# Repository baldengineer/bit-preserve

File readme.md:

# Bit Preserve
Recreating classic computer schematics. Let's convert all those random scanned PDFs into a modern, editiable and re-usable format.

# How it works
* Pick a system
* Find a schematic
* And start drawing!

This project uses [KiCad](http://kicad.org) for capturing schematics. 

# Notes
* If there are variants of the schematic, give them their own directory. 
* If you see a system you'd like to contribute but it isn't listed, submit a pull request. 
* If you start working on a system, please do a PR on the readme file in that directory and put your name there as "working on it." 
* Have suggestions or questions? Then [submit an issue](https://github.com/baldengineer/bit-preserve/issues)!

# More information
* Original project announcement [KiCon 2019](https://www.youtube.com/watch?v=fBaU4JZOVzk)
* See additional info on this [baldengineer.com post](https://www.baldengineer.com/bit-preserve-vintage-schematics-with-kicad.html).

# Rules - More like Guidelines
My goal is to have minimal rules. Right now I'd like to focus on documenting these systems *somewhere*. Someday, we might develop a style guide.

Bit Preserve has a few simple rules:
1. Do not upload bitmapped PDFs or images of original schematics. Instead, please link to repositories for that specific system instead.
2. Use KiCad's [Plot -> PDF] of the Schematic (not print!) when "done."
3. Add a link in the README to that PDF to make finding them easier.
4. Originally, we did not share symbol libraries between systems. (This was before KiCad changed how symbols get imported and linked in a schematic)
5. If you decide to re-create the PCB, **Please do NOT upload large binaries like STEP files**. Contact me if you want to include STEPs. (We'll do it as a submodule.)

# Questions or Ideas
Please, [submit an issue](https://github.com/baldengineer/bit-preserve/issues). In most cases, there is no need to email me. I want open discussions about how we move forward.

	-James
	@[baldengineer](https://baldengineer.com/baldengineer)

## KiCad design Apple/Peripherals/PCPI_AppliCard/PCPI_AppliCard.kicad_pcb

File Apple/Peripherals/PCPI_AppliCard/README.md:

# PCPI AppliCard

This is a clone of the PCPI AppliCard, a Z80 coprocessor card for the Apple II.
I've previously captured the [Microsoft Softcard](https://git.alfter.us/salfter/Microsoft_Softcard),
a simpler Z80 board that uses the Apple II's memory.  This board has its own
64K (expandable to 192K) connected directly to the Z80 and running at the same
speed.

The schematic was captured from published sources.  The PCB layout is based on
the component layout shown in a photo of the original board, but the connections
between components are my own work.  The new PCB, like the original, is a 2-layer
design.

I've not had a chance to build this.  DRC tells me the PCB matches the schematic.
I think my schematic capture is correct, but I don't have a working PCB to compare
against, so **use this at your own risk**.

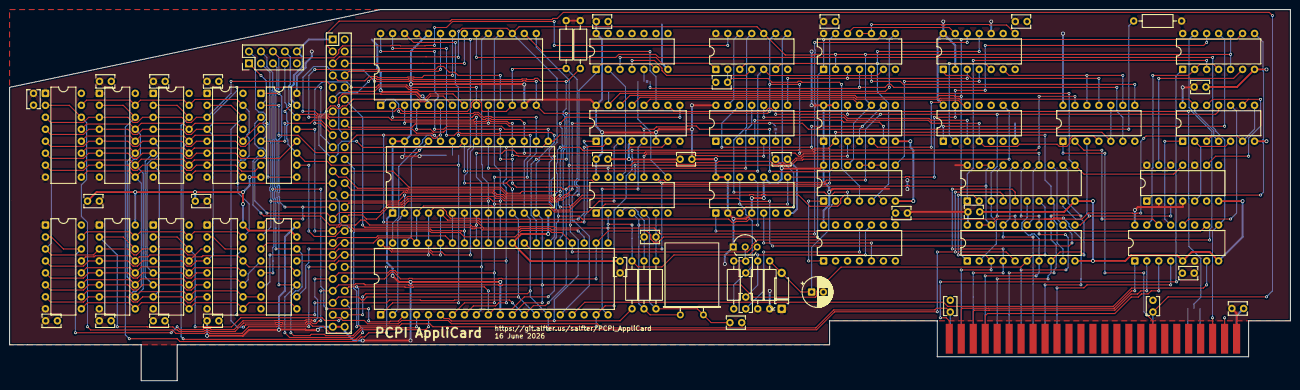
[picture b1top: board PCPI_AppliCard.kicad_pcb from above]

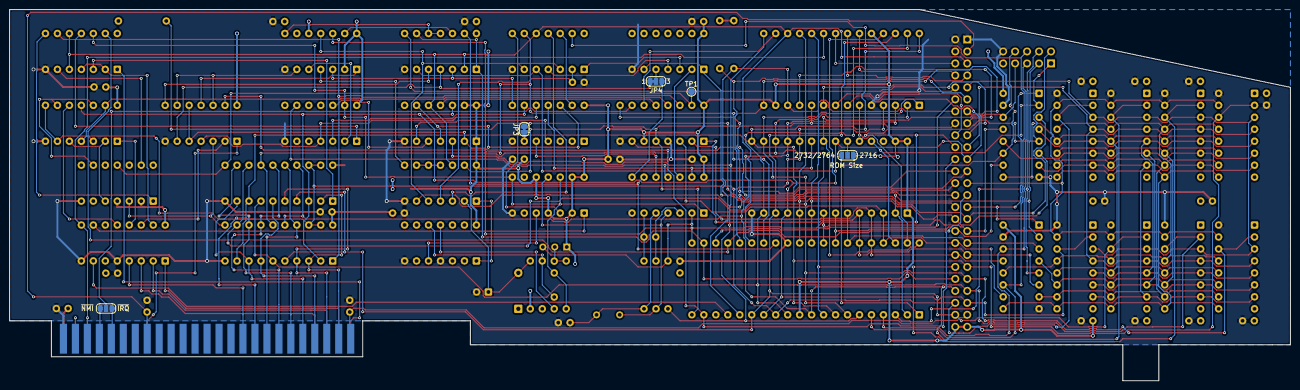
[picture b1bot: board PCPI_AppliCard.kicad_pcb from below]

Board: 2 copper layers, 271.8 x 78.7 mm, 82 parts (5 on the bottom side), 143 nets.

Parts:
C1, C2, C3, C4, C5, C6, C7, C8, C9, C10, C11, C13, C14, C15, C18, C19, C21, C22, C23, C24, C27, C28, C29, C30: 0.1 µF; C_Disc_D3.8mm_W2.6mm_P2.50mm
C12: 0.01 µF; C_Disc_D3.8mm_W2.6mm_P2.50mm
C16: 1000 pF; C_Disc_D3.8mm_W2.6mm_P2.50mm
C17, C31: 33 pF; C_Disc_D3.8mm_W2.6mm_P2.50mm
C20: 100 µF; CP_Radial_D6.3mm_P2.50mm
C25: 47 pF; C_Disc_D3.8mm_W2.6mm_P2.50mm
CR1: 1N4148; D_A-405_P7.62mm_Horizontal
JP1: IRQ/NMI; SolderJumper-3_P1.3mm_Open_RoundedPad1.0x1.5mm_NumberLabels
JP2: ROM_Size; SolderJumper-3_P1.3mm_Open_RoundedPad1.0x1.5mm_NumberLabels
JP3: SolderJumper_2_Bridged; SolderJumper-2_P1.3mm_Bridged_RoundedPad1.0x1.5mm
JP4: SolderJumper_3_Bridged12; SolderJumper-3_P1.3mm_Bridged12_RoundedPad1.0x1.5mm_NumberL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
P1: apple2-bus-edgeconn; Male_Card-Edge_50_pin__100_mil
P2: Conn_02x25_Counter_Clockwise; PinHeader_2x25_P2.54mm_Vertical_Counterclockwise
P3: Conn_02x05_Counter_Clockwise; PinHeader_2x05_P2.54mm_Vertical_Counterclockwise
Q1: 2N2907A; TO-92L_Inline_Wide
R1, R2, R3: 4.7 kΩ; R_Axial_DIN0207_L6.3mm_D2.5mm_P10.16mm_Horizontal
R4: 82 kΩ; R_Axial_DIN0207_L6.3mm_D2.5mm_P10.16mm_Horizontal
R5, R6: 1 kΩ; R_Axial_DIN0207_L6.3mm_D2.5mm_P10.16mm_Horizontal
R7: 27 Ω; R_Axial_DIN0207_L6.3mm_D2.5mm_P10.16mm_Horizontal
R8, R9: 10 kΩ; R_Axial_DIN0207_L6.3mm_D2.5mm_P10.16mm_Horizontal
TP1: TestPoint_Pad_D1.5mm
U1, U2, U3, U4, U5, U6, U7, U8: MK4164; DIP-16_W7.62mm
U9, U10: SN74LS158N; DIP-16_W7.62mm
U11: Z84C0006PEG; DIP-40_W15.24mm
U12: 2764; DIP-28_W15.24mm
U13: Z84C3006PEG; DIP-28_W15.24mm
U14, U19: SN74LS04N; DIP-14_W7.62mm
U15, U29: SN74LS138N; DIP-16_W7.62mm
U16, U28: SN74LS32N; DIP-14_W7.62mm
U17, U22, U27, U30: SN74LS74AN; DIP-14_W7.62mm
U18: SN74LS00N; DIP-14_W7.62mm
U20: SN74121N; DIP-14_W7.62mm
U21: SN74LS132N; DIP-14_W7.62mm
U23: SN74LS11N; DIP-14_W7.62mm
U24, U25: SN74LS374N; DIP-20_W7.62mm
U26: SN74LS393N; DIP-14_W7.62mm
U31: SN74LS125AN; DIP-14_W7.62mm
U32: SN74LS08N; DIP-14_W7.62mm
Y1: 12 MHz; Crystal_HC49-U_Horizontal

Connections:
+5V: C1.1, C2.1, C3.1, C4.1, C5.1, C6.1, C7.1, C8.1, C9.1, C10.1, C11.1, C13.1, C14.1, C15.1, C18.1, C19.1, C21.1, C22.1, C24.1, C27.1, C29.1, C30.1, CR1.1 (K), JP2.1 (A), P1.25 (+5V), P2.25, P2.26, Q1.1 (E), R1.1, R2.1, R3.1, R8.2, R9.1, U1.1 (~RFSH), U1.8 (VCC), U2.1 (~RFSH), U2.8 (VCC), U3.1 (~RFSH), U3.8 (VCC), U4.1 (~RFSH), U4.8 (VCC), U5.1 (~RFSH), U5.8 (VCC), U6.1 (~RFSH), U6.8 (VCC), U7.1 (~RFSH), U7.8 (VCC), U8.1 (~RFSH), U8.8 (VCC), U9.16 (VCC), U10.16 (VCC), U11.11 (V_{CC}), U12.1 (VPP), U12.27 (~PGM), U12.28 (VCC), U13.13 (IEI), U13.24 (VCC), U14.14 (VCC), U15.6 (E3), U15.16 (VCC), U16.14 (VCC), U17.2 (D), U17.4 (~S), U17.10 (~S), U17.13 (~R), U17.14 (VCC), U18.14 (VCC), U19.14 (VCC), U20.14 (VCC), U21.14 (VCC), U22.1 (~R), U22.13 (~R), U22.14 (VCC), U23.14 (VCC), U24.20 (VCC), U25.20 (VCC), U26.14 (VCC), U27.2 (D), U27.10 (~S), U27.14 (VCC), U28.14 (VCC), U29.6 (E3), U29.16 (VCC), U30.2 (D), U30.4 (~S), U30.10 (~S), U30.12 (D), U30.14 (VCC), U31.14 (VCC), U32.14 (VCC)
+12V: C28.1, P1.50 (+12V), P2.24
-12V: C23.1, P1.33 (-12V), P2.2
/Host_Interface/~ADMA: P1.24 (~DMAOUT), P1.27 (~DMAIN)
A0: P2.16, U10.3 (I1a), U11.30 (A_{0}), U12.10 (A0), U13.18 (CS0)
A1: P2.35, U10.6 (I1b), U11.31 (A_{1}), U12.9 (A1), U13.19 (CS1)
A2: P2.17, U10.13 (I1c), U11.32 (A_{2}), U12.8 (A2)
A3: P2.34, U10.10 (I1d), U11.33 (A_{3}), U12.7 (A3)
A4: P2.18, U9.3 (I1a), U11.34 (A_{4}), U12.6 (A4)
A5: P2.19, U9.6 (I1b), U11.35 (A_{5}), U12.5 (A5), U15.1 (A0)
A6: P2.32, U9.13 (I1c), U11.36 (A_{6}), U12.4 (A6), U15.2 (A1)
A7: P2.33, U9.10 (I1d), U11.37 (A_{7}), U12.3 (A7), U15.3 (A2)
A8: P3.1, U10.2 (I0a), U11.38 (A_{8}), U12.25 (A8)
A9: P3.10, U10.5 (I0b), U11.39 (A_{9}), U12.24 (A9)
A10: P3.4, U10.14 (I0c), U11.40 (A_{10}), U12.21 (A10)
A11: JP2.3 (B), P3.7, U10.11 (I0d), U11.1 (A_{11})
A12: P3.2, U9.2 (I0a), U11.2 (A_{12}), U12.2 (A12)
A13: P3.9, U9.5 (I0b), U11.3 (A_{13})
A14: P3.3, U9.14 (I0c), U11.4 (A_{14})
A15: P3.8, U9.11 (I0d), U11.5 (A_{15}), U19.13
AA0: P1.2 (A0), U29.1 (A0)
AA1: P1.3 (A1), U29.2 (A1)
AA2: P1.4 (A2), U29.3 (A2)
AD0: P1.49 (D0), U24.3 (D0), U25.2 (O0)
AD1: P1.48 (D1), U24.4 (D1), U25.5 (O1)
AD2: P1.47 (D2), U24.7 (D2), U25.6 (O2)
AD3: P1.46 (D3), U24.8 (D3), U25.9 (O3)
AD4: P1.45 (D4), U24.13 (D4), U25.12 (O4)
AD5: P1.44 (D5), U24.14 (D5), U25.15 (O5)
AD6: P1.43 (D6), U24.17 (D6), U25.16 (O6)
AD7: P1.42 (D7), P2.28, U8.2 (DIN), U8.14 (DOUT), U11.13 (D_{7}), U12.19 (D7), U13.4 (D7), U24.18 (D7), U24.19 (O7), U25.18 (D7), U25.19 (O7), U31.3, U31.6, U31.8
CLKI0: P2.47, U13.23 (CLK/TRG0)
CLKI1: P2.4, U13.22 (CLK/TRG1)
CLKI2: P2.48, U13.21 (CLK/TRG2)
CLOCK: R7.2, U11.6 (CLK), U13.15 (CLK), U22.3 (C)
CLOCK0: P2.10, U13.7 (ZC/TO0)
CLOCK1: P2.42, U13.8 (ZC/TO1)
CLOCK2: P2.9, U13.9 (ZC/TO2)
D0: P2.23, U7.2 (DIN), U7.14 (DOUT), U11.14 (D_{0}), U12.11 (D0), U13.25 (D0), U22.12 (D), U24.2 (O0), U25.3 (D0), U31.11
D1: P2.27, U5.2 (DIN), U5.14 (DOUT), U11.15 (D_{1}), U12.12 (D1), U13.26 (D1), U24.5 (O1), U25.4 (D1)
D2: P2.22, U3.2 (DIN), U3.14 (DOUT), U11.12 (D_{2}), U12.13 (D2), U13.27 (D2), U24.6 (O2), U25.7 (D2)
D3: P2.20, U2.2 (DIN), U2.14 (DOUT), U11.8 (D_{3}), U12.15 (D3), U13.28 (D3), U24.9 (O3), U25.8 (D3)
D4: P2.21, U1.2 (DIN), U1.14 (DOUT), U11.7 (D_{4}), U12.16 (D4), U13.1 (D4), U24.12 (O4), U25.13 (D4)
D5: P2.31, U4.2 (DIN), U4.14 (DOUT), U11.9 (D_{5}), U12.17 (D5), U13.2 (D5), U24.15 (O5), U25.14 (D5)
D6: P2.29, U6.2 (DIN), U6.14 (DOUT), U11.10 (D_{6}), U12.18 (D6), U13.3 (D6), U24.16 (O6), U25.17 (D6)
GND: C1.2, C2.2, C3.2, C4.2, C5.2, C6.2, C7.2, C8.2, C9.2, C10.2, C11.2, C13.2, C14.2, C15.2, C18.2, C19.2, C20.2, C21.2, C22.2, C23.2, C24.2, C25.2, C27.2, C28.2, C29.2, C30.2, C31.2, P1.26 (GND), P2.1, P2.50, P3.6, U1.16 (VSS), U2.16 (VSS), U3.16 (VSS), U4.16 (VSS), U5.16 (VSS), U6.16 (VSS), U7.16 (VSS), U8.16 (VSS), U9.8 (GND), U9.15 (E), U10.8 (GND), U10.15 (E), U11.29 (GND), U12.14 (GND), U13.5 (GND), U14.7 (GND), U15.4 (E1), U15.8 (GND), U16.7 (GND), U17.7 (GND), U18.7 (GND), U19.7 (GND), U20.4 (A2), U20.7 (GND), U21.7 (GND), U22.7 (GND), U23.7 (GND), U24.10 (GND), U25.10 (GND), U26.7 (GND), U27.7 (GND), U28.7 (GND), U29.5 (E2), U29.8 (GND), U30.7 (GND), U31.7 (GND), U32.7 (GND)
MA0: U1.5 (A0), U2.5 (A0), U3.5 (A0), U4.5 (A0), U5.5 (A0), U6.5 (A0), U7.5 (A0), U8.5 (A0), U10.4 (Za)
MA1: U1.7 (A1), U2.7 (A1), U3.7 (A1), U4.7 (A1), U5.7 (A1), U6.7 (A1), U7.7 (A1), U8.7 (A1), U10.7 (Zb)
MA2: U1.6 (A2), U2.6 (A2), U3.6 (A2), U4.6 (A2), U5.6 (A2), U6.6 (A2), U7.6 (A2), U8.6 (A2), U10.12 (Zc)
MA3: U1.12 (A3), U2.12 (A3), U3.12 (A3), U4.12 (A3), U5.12 (A3), U6.12 (A3), U7.12 (A3), U8.12 (A3), U10.9 (Zd)
MA4: U1.11 (A4), U2.11 (A4), U3.11 (A4), U4.11 (A4), U5.11 (A4), U6.11 (A4), U7.11 (A4), U8.11 (A4), U9.4 (Za)
MA5: U1.10 (A5), U2.10 (A5), U3.10 (A5), U4.10 (A5), U5.10 (A5), U6.10 (A5), U7.10 (A5), U8.10 (A5), U9.7 (Zb)
MA6: U1.13 (A6), U2.13 (A6), U3.13 (A6), U4.13 (A6), U5.13 (A6), U6.13 (A6), U7.13 (A6), U8.13 (A6), U9.12 (Zc)
MA7: U1.9 (A7), U2.9 (A7), U3.9 (A7), U4.9 (A7), U5.9 (A7), U6.9 (A7), U7.9 (A7), U8.9 (A7), U9.9 (Zd)
unnamed: C12.1, R5.1, U14.6
unnamed: C12.2, R6.1, U14.3
unnamed: C25.1, U19.2, U21.4
unnamed: C31.1, R5.2, U14.5, Y1.1
unnamed: C20.1, CR1.2 (A), R9.2, U21.2
unnamed: JP2.2 (C), U12.23 (A11)
unnamed: JP3.1 (A), U18.6
unnamed: JP4.3 (B), U14.8
unnamed: JP4.2 (C), U16.5
unnamed: C17.2, Q1.2 (B), R4.2
unnamed: Q1.3 (C), R7.1, U14.2
unnamed: U14.10, U18.5
unnamed: U14.12, U16.2
unnamed: U16.3, U19.1
unnamed: U16.4, U19.4
unnamed: U17.3 (C), U19.8
unnamed: U17.5 (Q), U20.5 (B)
unnamed: R6.2, U14.4, U17.11 (C), Y1.2
unnamed: U18.13, U19.12
unnamed: U19.11, U21.3
unnamed: C16.2, R8.1, U20.10 (Cext)
unnamed: C16.1, U20.11 (R/Cext)
unnamed: U20.1 (~Q), U21.1
unnamed: U21.9, U21.10, U21.11
unnamed: U22.5 (Q), U26.12 (MR)
unnamed: U18.4, U22.6 (~Q)
unnamed: U18.12, U22.4 (~S), U22.9 (Q)
unnamed: U23.5, U28.8
unnamed: U24.11 (Cp), U28.3, U30.3 (C)
unnamed: U25.1 (OE), U32.3
unnamed: U26.1 (CP), U32.11
unnamed: U26.2 (MR), U27.5 (Q)
unnamed: U18.9, U26.3 (Q0)
unnamed: U18.10, U26.4 (Q1), U28.4
unnamed: U14.11, U26.9 (Q2)
unnamed: U27.6 (~Q), U28.9, U28.12
unnamed: U27.1 (~R), U28.11
unnamed: U21.8, U27.4 (~S)
unnamed: U19.3, U19.6, U21.5, U27.11 (C)
unnamed: U23.10, U23.11, U27.8 (~Q)
unnamed: U23.12, U27.13 (~R)
unnamed: U29.15 (O0), U32.2, U32.4
unnamed: U28.2, U29.14 (O1)
unnamed: U29.13 (O2), U31.1
unnamed: U29.12 (O3), U31.10
unnamed: U30.5 (Q), U31.2, U31.5
unnamed: U30.1 (~R), U32.8
unnamed: U30.9 (Q), U31.9, U31.12
unnamed: U30.13 (~R), U32.6
R/~W: P1.18 (R/~W), U28.1
SEL: P2.15, U9.1 (S), U10.1 (S)
SELOUT: P2.36, U16.1, U16.6
~AINT: P1.23 (~INTOUT), P1.28 (~INTIN), U13.20 (CLK/TRG3), U29.9 (O6)
~AIRQ: JP1.3 (B), P1.30 (~IRQ)
~ANMI: JP1.1 (A), P1.29 (~NMI)
~BUSACK: P2.45, U11.23 (~BUSACK)
~BUSREQ: P2.6, R2.2, U11.25 (~BUSREQ)
~CASOUT: P2.38, U21.6
~CAS: P2.13, U1.15 (~CAS), U2.15 (~CAS), U3.15 (~CAS), U4.15 (~CAS), U5.15 (~CAS), U6.15 (~CAS), U7.15 (~CAS), U8.15 (~CAS)
~CHAINOUT: P2.8, U13.11 (IEO)
~CLOCK: C17.1, R4.1, U14.1, U17.8 (~Q), U17.12 (D), U26.13 (CP), U32.12
~CS0: TP1.1 (1_1), U15.15 (O0), U25.11 (Cp), U30.11 (C)
~CS1: U15.14 (O1), U24.1 (OE), U32.9
~CS2: U15.13 (O2), U31.4, U31.13
~CS3: U15.12 (O3), U22.11 (C)
~CS4: U13.16 (~CE), U15.11 (O4)
~CS5: JP1.2 (C), U15.10 (O5)
~CS6: P2.39, U15.9 (O6)
~CS7: P2.12, U15.7 (O7)
~DEVSEL: P1.41 (~DEVSEL), U29.4 (E1)
~GENMREQ: JP4.1 (A), U23.4, U28.6
~GENRFSH: U18.8, U23.3, U27.3 (C)
~INT: P2.44, R3.2, U11.16 (~INT), U13.12 (~INT)
~IORQ: P2.43, U11.20 (~IORQ), U13.10 (~IORQ), U15.5 (E2), U21.13
~IOSEL: P1.1 (~IOSEL), U32.1
~M1: P2.7, U11.27 (~M1), U13.14 (~M1), U19.9, U28.13
~MREQ: P2.40, U11.19 (~MREQ), U22.2 (D), U28.5, U28.10
~NMI: U11.17 (~NMI), U29.7 (O7)
~PROM: U12.20 (~CE), U14.13, U18.11
~RAMWROUT: P2.46, U23.8
~RAMWR: P2.5, U1.3 (~WRITE), U2.3 (~WRITE), U3.3 (~WRITE), U4.3 (~WRITE), U5.3 (~WRITE), U6.3 (~WRITE), U7.3 (~WRITE), U8.3 (~WRITE)
~RAS: P2.11, U1.4 (~RAS), U2.4 (~RAS), U3.4 (~RAS), U4.4 (~RAS), U5.4 (~RAS), U6.4 (~RAS), U7.4 (~RAS), U8.4 (~RAS), U12.22 (~OE), U19.5, U23.6
~RD: P2.41, U11.21 (~RD), U13.6 (~RD), U27.12 (D)
~RESET: P2.3, U11.26 (~RESET), U13.17 (~RESET), U19.10, U21.12, U22.10 (~S), U23.2, U32.5, U32.10
~RES: U17.1 (~R), U29.10 (O5)
~RFSH: U11.28 (~RFSH), U14.9, U23.13
~WAITOUT: JP3.2 (B), P2.37, R1.2
~WAIT: P2.14, U11.24 (~WAIT), U32.13
~WR: P2.30, U11.22 (~WR), U23.1, U23.9

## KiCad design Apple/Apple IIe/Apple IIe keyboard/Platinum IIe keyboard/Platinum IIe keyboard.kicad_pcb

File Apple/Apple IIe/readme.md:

# Apple IIe notes

This is a directory for a KiCad project for the Apple IIe.

Schematics currently available:
* Apple IIe (NTSC) schematic 050-0051-D - captured by [@rjhelms](https://github.com/rjhelms)

## Schematic sources

* [Apple IIe (NTSC) schematic 050-0051-D](https://mirrors.apple2.org.za/ftp.apple.asimov.net/documentation/hardware/schematics/apple_iie_ntsc_schematic.pdf)
* [Apple IIe (keyboard) schematic](https://downloads.reactivemicro.com/Apple%20II%20Items/Hardware/IIe/Schematic/Apple%20IIe%20Schematic%20-%20Keyboard.jpg)

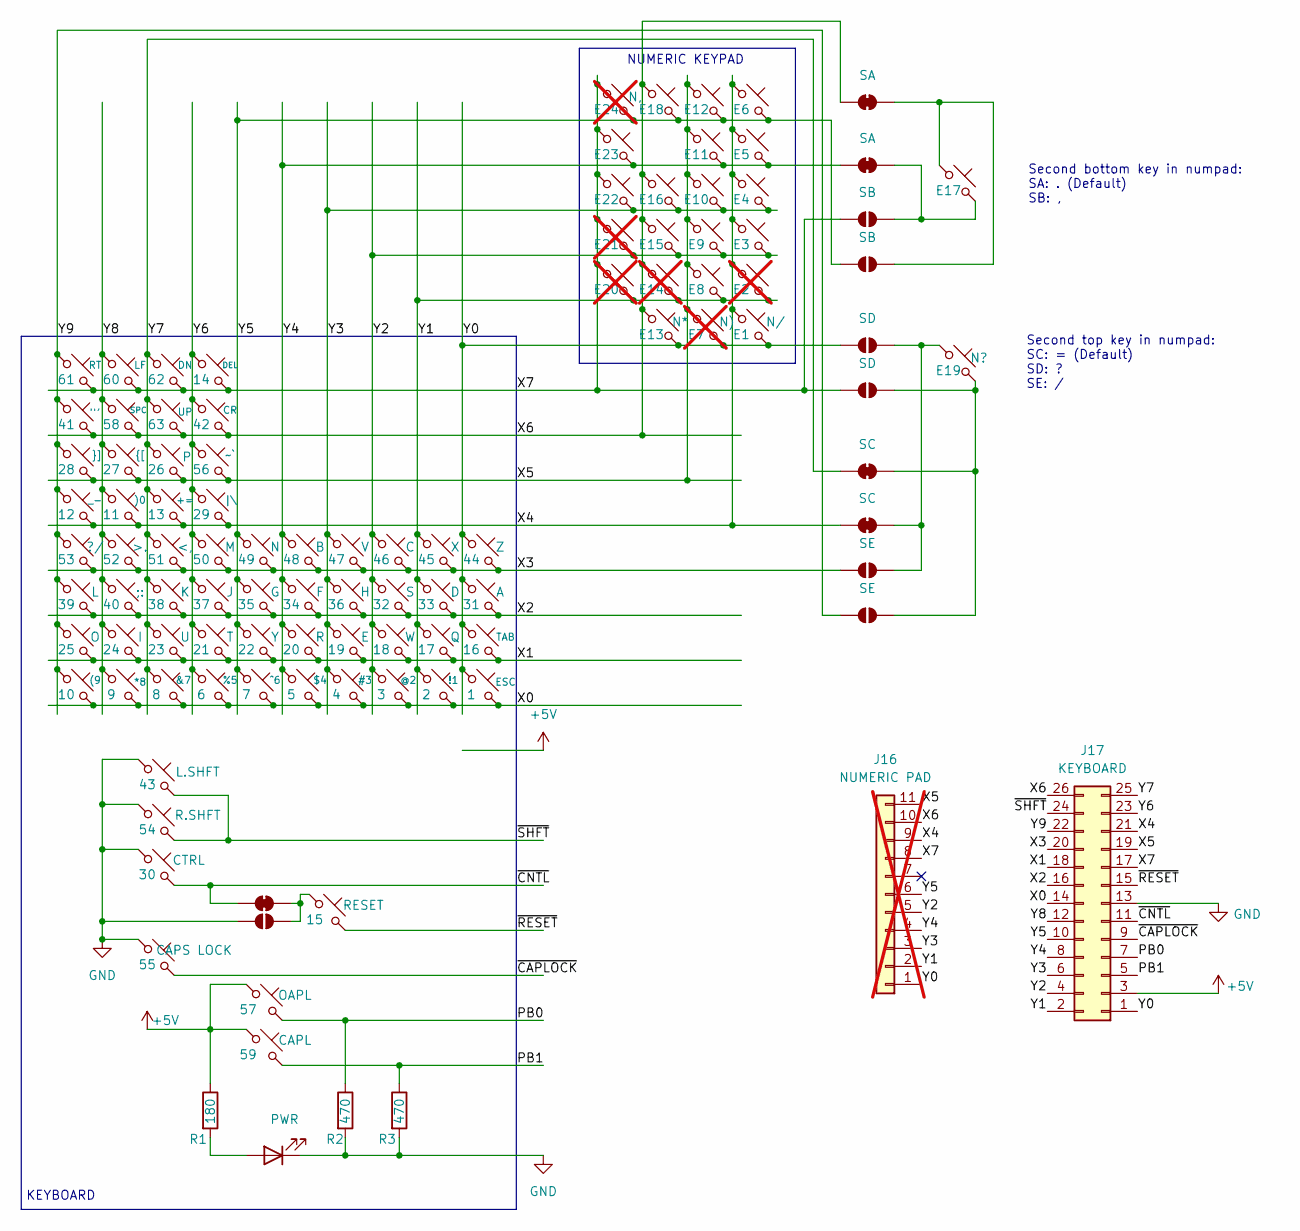
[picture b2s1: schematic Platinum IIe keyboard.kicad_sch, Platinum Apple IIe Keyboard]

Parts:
D1: PWR; LED_D3.0mm_Clear
J16: NUMERIC PAD; not fitted
J17: KEYBOARD; 26way_P1.27mm_EB50
JP1, JP6: SE; SolderJumper-Open_TriangularPad1.0x1.5mm
JP2, JP4: SC; SolderJumper-Closed_TriangularPad1.0x1.5mm
JP3, JP5: SD; SolderJumper-Open_TriangularPad1.0x1.5mm
JP7, JP8: SA; SolderJumper-Closed_TriangularPad1.0x1.5mm
JP9, JP10: SB; SolderJumper-Open_TriangularPad1.0x1.5mm
JP11: CNRE; SolderJumper-Closed_TriangularPad1.0x1.5mm
JP12: RESE; SolderJumper-Open_TriangularPad1.0x1.5mm
R1: 180; R_Axial_DIN0309_L9.0mm_D3.2mm_P12.70mm_Horizontal
R2, R3: 470; R_Axial_DIN0309_L9.0mm_D3.2mm_P12.70mm_Horizontal
SW1: E6; SW_AlpsSKCC_1.00u_rev
SW2: E12; SW_AlpsSKCC_1.00u_rev
SW3: E18; SW_AlpsSKCC_1.00u_rev
SW4: E24; SW_AlpsSKCC_1.00u_rev; not fitted
SW5: E23; SW_AlpsSKCC_1.00u_rev
SW6: E17; SW_AlpsSKCC_1.00u
SW7: E11; SW_AlpsSKCC_1.00u_rev
SW8: E5; SW_AlpsSKCC_1.00u_rev
SW9: E22; SW_AlpsSKCC_1.00u_rev
SW10: E21; SW_AlpsSKCC_1.00u_rev; not fitted
SW11: E20; SW_AlpsSKCC_1.00u_rev; not fitted
SW12: E19; SW_AlpsSKCC_1.00u_rev
SW13: E16; SW_AlpsSKCC_1.00u_rev
SW14: E15; SW_AlpsSKCC_1.00u_rev
SW15: E14; SW_AlpsSKCC_1.00u_rev; not fitted
SW16: E13; SW_AlpsSKCC_1.00u_rev
SW17: E7; SW_AlpsSKCC_1.00u_rev; not fitted
SW18: E8; SW_AlpsSKCC_1.00u_rev
SW19: E9; SW_AlpsSKCC_1.00u_rev
SW20: E10; SW_AlpsSKCC_1.00u_rev
SW21: E4; SW_AlpsSKCC_1.00u_rev
SW22: E3; SW_AlpsSKCC_2.00u_rev
SW23: E2; SW_AlpsSKCC_1.00u_rev; not fitted
SW24: E1; SW_AlpsSKCC_1.00u_rev
SW25: 61; SW_AlpsSKCC_1.00u
SW26: 60; SW_AlpsSKCC_1.00u
SW27: 62; SW_AlpsSKCC_1.00u
SW28: 14; SW_AlpsSKCC_1.50u
SW29: 41; SW_AlpsSKCC_1.00u
SW30: 28; SW_AlpsSKCC_1.00u
SW31: 12; SW_AlpsSKCC_1.00u
SW32: 53; SW_AlpsSKCC_1.00u
SW33: 52; SW_AlpsSKCC_1.00u
SW34: 51; SW_AlpsSKCC_1.00u
SW35: 50; SW_AlpsSKCC_1.00u
SW36: 49; SW_AlpsSKCC_1.00u
SW37: 48; SW_AlpsSKCC_1.00u
SW38: 47; SW_AlpsSKCC_1.00u
SW39: 46; SW_AlpsSKCC_1.00u
SW40: 45; SW_AlpsSKCC_1.00u
SW41: 44; SW_AlpsSKCC_1.00u
SW42: 42; SW_AlpsSKCC_1.75u
SW43: 56; SW_AlpsSKCC_1.00u
SW44: 29; SW_AlpsSKCC_1.00u
SW45: 13; SW_AlpsSKCC_1.00u
SW46: 26; SW_AlpsSKCC_1.00u
SW47: 63; SW_AlpsSKCC_1.00u
SW48: 11; SW_AlpsSKCC_1.00u
SW49: 27; SW_AlpsSKCC_1.00u
SW50: 58; SW_AlpsSKCC_1.00u
SW51: 39; SW_AlpsSKCC_1.00u
SW52: 40; SW_AlpsSKCC_1.00u
SW53: 38; SW_AlpsSKCC_1.00u
SW54: 37; SW_AlpsSKCC_1.00u
SW55: 35; SW_AlpsSKCC_1.00u
SW56: 34; SW_AlpsSKCC_1.00u
SW57: 36; SW_AlpsSKCC_1.00u
SW58: 32; SW_AlpsSKCC_1.00u
SW59: 33; SW_AlpsSKCC_1.00u
SW60: 31; SW_AlpsSKCC_1.00u
SW61: 25; SW_AlpsSKCC_1.00u
SW62: 24; SW_AlpsSKCC_1.00u
SW63: 23; SW_AlpsSKCC_1.00u
SW64: 21; SW_AlpsSKCC_1.00u
SW65: 22; SW_AlpsSKCC_1.00u
SW66: 20; SW_AlpsSKCC_1.00u
SW67: 19; SW_AlpsSKCC_1.00u
SW68: 18; SW_AlpsSKCC_1.00u
SW69: 17; SW_AlpsSKCC_1.00u
SW70: 16; SW_AlpsSKCC_1.50u
SW71: 10; SW_AlpsSKCC_1.00u
SW72: 9; SW_AlpsSKCC_1.00u
SW73: 8; SW_AlpsSKCC_1.00u
SW74: 6; SW_AlpsSKCC_1.00u
SW75: 7; SW_AlpsSKCC_1.00u
SW76: 5; SW_AlpsSKCC_1.00u
SW77: 4; SW_AlpsSKCC_1.00u
SW78: 3; SW_AlpsSKCC_1.00u
SW79: 2; SW_AlpsSKCC_1.00u
SW80: 1; SW_AlpsSKCC_1.00u
SW81: 15; SW_AlpsSKCC_1.00u
SW82: 59; SW_AlpsSKCC_1.00u
SW83: 57; SW_AlpsSKCC_1.75u
SW84: 55; SW_AlpsSKCC_1.00u
SW85: 30; SW_AlpsSKCC_1.75u
SW86: 54; SW_AlpsSKCC_2.25u
SW87: 43; SW_AlpsSKCC_2.25u

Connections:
+5V: J17.3, R1.1, SW82.1, SW83.1
/PB0: J17.7, R2.1, SW83.2
/PB1: J17.5, R3.1, SW82.2
/X0: J17.14, SW71.2, SW72.2, SW73.2, SW74.2, SW75.2, SW76.2, SW77.2, SW78.2, SW79.2, SW80.2
/X1: J17.18, SW61.2, SW62.2, SW63.2, SW64.2, SW65.2, SW66.2, SW67.2, SW68.2, SW69.2, SW70.2
/X2: J17.16, SW51.2, SW52.2, SW53.2, SW54.2, SW55.2, SW56.2, SW57.2, SW58.2, SW59.2, SW60.2
/X3: J17.20, JP1.1 (A), SW32.2, SW33.2, SW34.2, SW35.2, SW36.2, SW37.2, SW38.2, SW39.2, SW40.2, SW41.2
/X4: J16.9, J17.21, JP2.1 (A), SW1.1, SW8.1, SW21.1, SW22.1, SW23.1, SW24.1, SW31.2, SW44.2, SW45.2, SW48.2
/X5: J16.11, J17.19, SW2.1, SW7.1, SW17.1, SW18.1, SW19.1, SW20.1, SW30.2, SW43.2, SW46.2, SW49.2
/X6: J16.10, J17.26, JP7.1 (A), SW3.1, SW13.1, SW14.1, SW15.1, SW16.1, SW29.2, SW42.2, SW47.2, SW50.2
/X7: J16.8, J17.17, JP5.1 (A), JP9.1 (A), SW4.1, SW5.1, SW9.1, SW10.1, SW11.1, SW25.2, SW26.2, SW27.2, SW28.2
/Y0: J16.1, J17.1, JP3.1 (A), SW16.2, SW17.2, SW24.2, SW41.1, SW60.1, SW70.1, SW80.1
/Y1: J16.2, J17.2, SW11.2, SW15.2, SW18.2, SW23.2, SW40.1, SW59.1, SW69.1, SW79.1
/Y2: J16.5, J17.4, SW10.2, SW14.2, SW19.2, SW22.2, SW39.1, SW58.1, SW68.1, SW78.1
/Y3: J16.3, J17.6, SW9.2, SW13.2, SW20.2, SW21.2, SW38.1, SW57.1, SW67.1, SW77.1
/Y4: J16.4, J17.8, JP8.1 (A), SW5.2, SW7.2, SW8.2, SW37.1, SW56.1, SW66.1, SW76.1
/Y5: J16.6, J17.10, JP10.1 (A), SW1.2, SW2.2, SW3.2, SW4.2, SW36.1, SW55.1, SW65.1, SW75.1
/Y6: J17.23, SW28.1, SW35.1, SW42.1, SW43.1, SW44.1, SW54.1, SW64.1, SW74.1
/Y7: J17.25, JP4.1 (A), SW27.1, SW34.1, SW45.1, SW46.1, SW47.1, SW53.1, SW63.1, SW73.1
/Y8: J17.12, SW26.1, SW33.1, SW48.1, SW49.1, SW50.1, SW52.1, SW62.1, SW72.1
/Y9: J17.22, JP6.1 (A), SW25.1, SW29.1, SW30.1, SW31.1, SW32.1, SW51.1, SW61.1, SW71.1
/~CAPLOCK: J17.9, SW84.2
/~CNTL: J17.11, JP11.1 (A), SW85.2
/~RESET: J17.15, SW81.2
/~SHFT: J17.24, SW86.2, SW87.2
GND: D1.1 (K), J17.13, JP12.2 (B), R2.2, R3.2, SW84.1, SW85.1, SW86.1, SW87.1
unnamed: D1.2 (A), R1.2
unnamed: JP1.2 (B), JP2.2 (B), JP3.2 (B), SW12.1
unnamed: JP4.2 (B), JP5.2 (B), JP6.2 (B), SW12.2
unnamed: JP8.2 (B), JP9.2 (B), SW6.2
unnamed: JP7.2 (B), JP10.2 (B), SW6.1
unnamed: JP11.2 (B), JP12.1 (A), SW81.1

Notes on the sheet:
Second top key in numpad: SC: = (Default) SD: ? SE: /
KEYBOARD
Second bottom key in numpad: SA: . (Default) SB: ,
NUMERIC KEYPAD

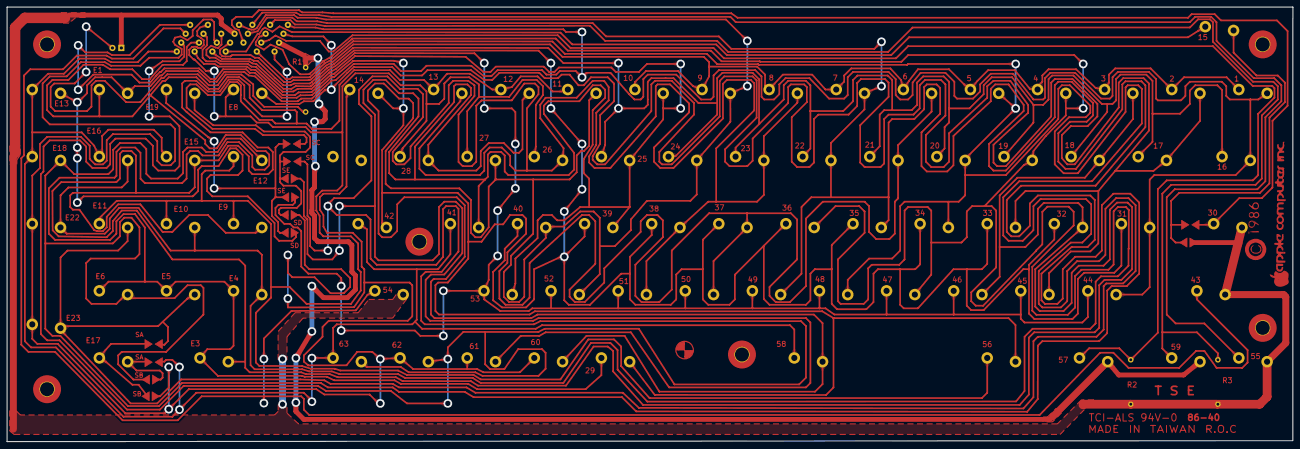
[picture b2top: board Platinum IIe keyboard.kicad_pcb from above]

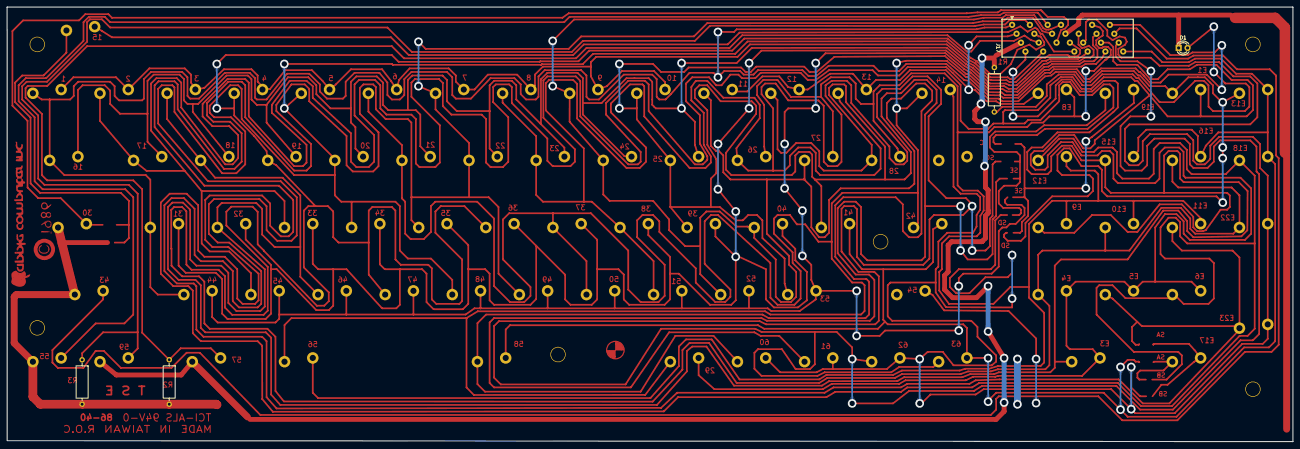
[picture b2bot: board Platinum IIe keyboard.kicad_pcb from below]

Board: 2 copper layers, 367.5 x 124.2 mm, 99 parts (87 on the bottom side), 32 nets.

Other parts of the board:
SW999: SW_AlpsSKCC_1.00u

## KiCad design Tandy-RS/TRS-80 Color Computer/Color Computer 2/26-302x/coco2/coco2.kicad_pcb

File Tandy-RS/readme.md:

# Tandy / Radio Shack
  * [TRS-80 Color Computer 2](https://github.com/baldengineer/bit-preserve/tree/main/Tandy-RS/TRS-80%20Color%20Computer/Color%20Computer%202)
    * Schematic 26-3134 / 26-3136
    * Schematic & PCB 26-3134A / 26-3136A
    * Schematic & PCB 26-3134B / 26-3136B
    * Schematic & PCB 26-3026 & 26-3027
  * [Tandy Color Computer 3](https://github.com/baldengineer/bit-preserve/tree/main/Tandy-RS/TRS-80%20Color%20Computer/Color%20Computer%203)
    * [Schematic & PCB 26-3334](https://github.com/baldengineer/bit-preserve/tree/main/Tandy-RS/TRS-80%20Color%20Computer/Color%20Computer%203/26-3334)
  * [TRS-80 MC10](https://github.com/baldengineer/bit-preserve/tree/main/Tandy-RS/TRS-80%20MC-10) [PDF](https://github.com/baldengineer/bit-preserve/blob/main/Tandy-RS/TRS-80%20MC-10/TRS-80%20MC-10.pdf)
  * [TRS-80 Model 100](https://github.com/hzeller/trs80-100-schematic/tree/b0950a775f76e6d70d48e391a3d07f2d41e703c8) (As a sub-module)
# System Wishlists
  * TRS-80 Model I
  * TRS-80 Model II
  * TRS-80 Model III

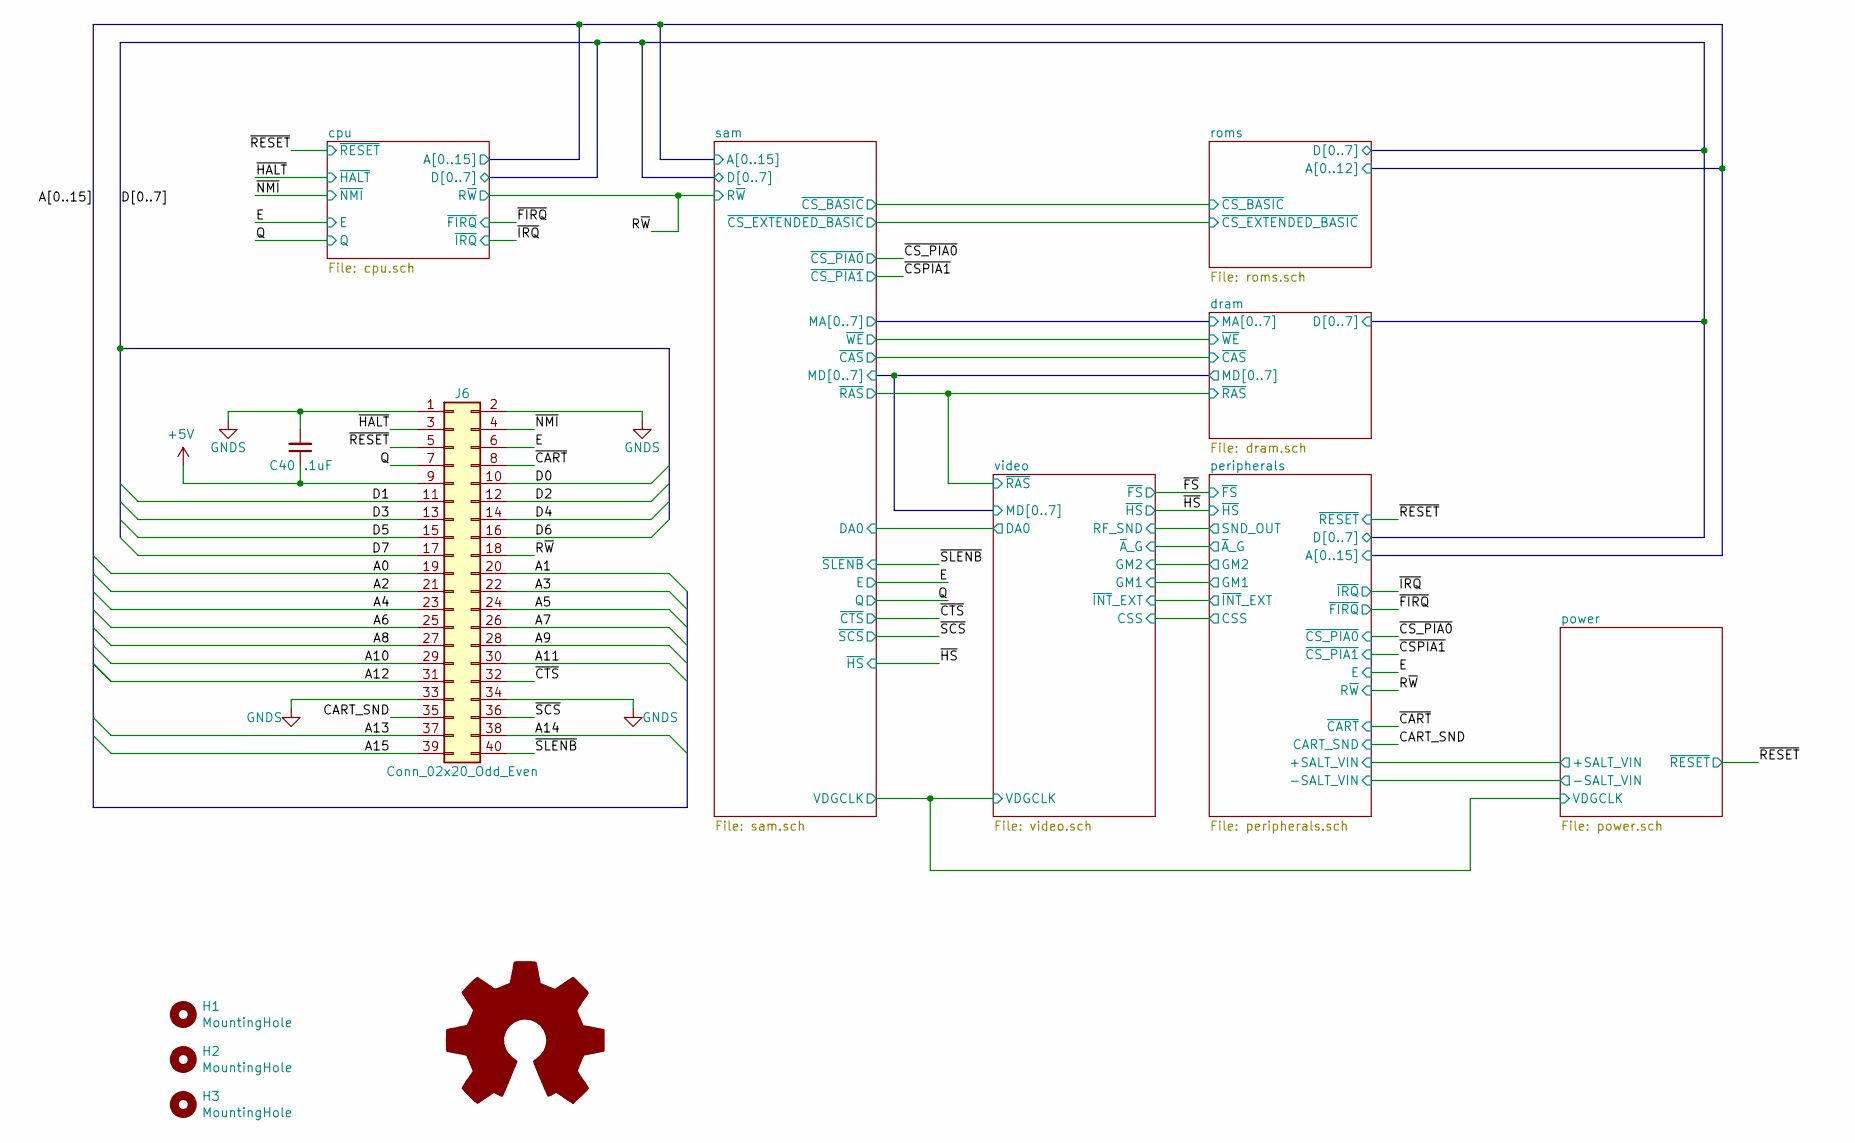
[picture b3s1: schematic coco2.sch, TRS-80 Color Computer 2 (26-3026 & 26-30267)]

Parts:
C40: .1uF; C_Axial_L3.8mm_D2.6mm_P10.00mm_Horizontal; Manufacturer part# A104K15X7RF5TAA
H1: MountingHole; MountingHole_4.5mm
H2, H3: MountingHole; MountingHole_4mm
J6: Conn_02x20_Odd_Even; EBC20DRAS; Manufacturer part# EBC20DRAS

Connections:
+5V: C40.1, J6.9; also elsewhere on the board
/A0: J6.19; also elsewhere on the board
/A1: J6.20; also elsewhere on the board
/A2: J6.21; also elsewhere on the board
/A3: J6.22; also elsewhere on the board
/A4: J6.23; also elsewhere on the board
/A5: J6.24; also elsewhere on the board
/A6: J6.25; also elsewhere on the board
/A7: J6.26; also elsewhere on the board
/A8: J6.27; also elsewhere on the board
/A9: J6.28; also elsewhere on the board
/A10: J6.29; also elsewhere on the board
/A11: J6.30; also elsewhere on the board
/A12: J6.31; also elsewhere on the board
/A13: J6.37; also elsewhere on the board
/A14: J6.38; also elsewhere on the board
/A15: J6.39; also elsewhere on the board
/CART_SND: J6.35; also elsewhere on the board
/D0: J6.10; also elsewhere on the board
/D1: J6.11; also elsewhere on the board
/D2: J6.12; also elsewhere on the board
/D3: J6.13; also elsewhere on the board
/D4: J6.14; also elsewhere on the board
/D5: J6.15; also elsewhere on the board
/D6: J6.16; also elsewhere on the board
/D7: J6.17; also elsewhere on the board
/E: J6.6; also elsewhere on the board
/Q: J6.7; also elsewhere on the board
/R~W: J6.18; also elsewhere on the board
/~CART: J6.8; also elsewhere on the board
/~CTS: J6.32; also elsewhere on the board
/~HALT: J6.3; also elsewhere on the board
/~NMI: J6.4; also elsewhere on the board
/~RESET: J6.5; also elsewhere on the board
/~SCS: J6.36; also elsewhere on the board
/~SLENB: J6.40; also elsewhere on the board
GNDS: C40.2, J6.1, J6.2, J6.33, J6.34; also elsewhere on the board

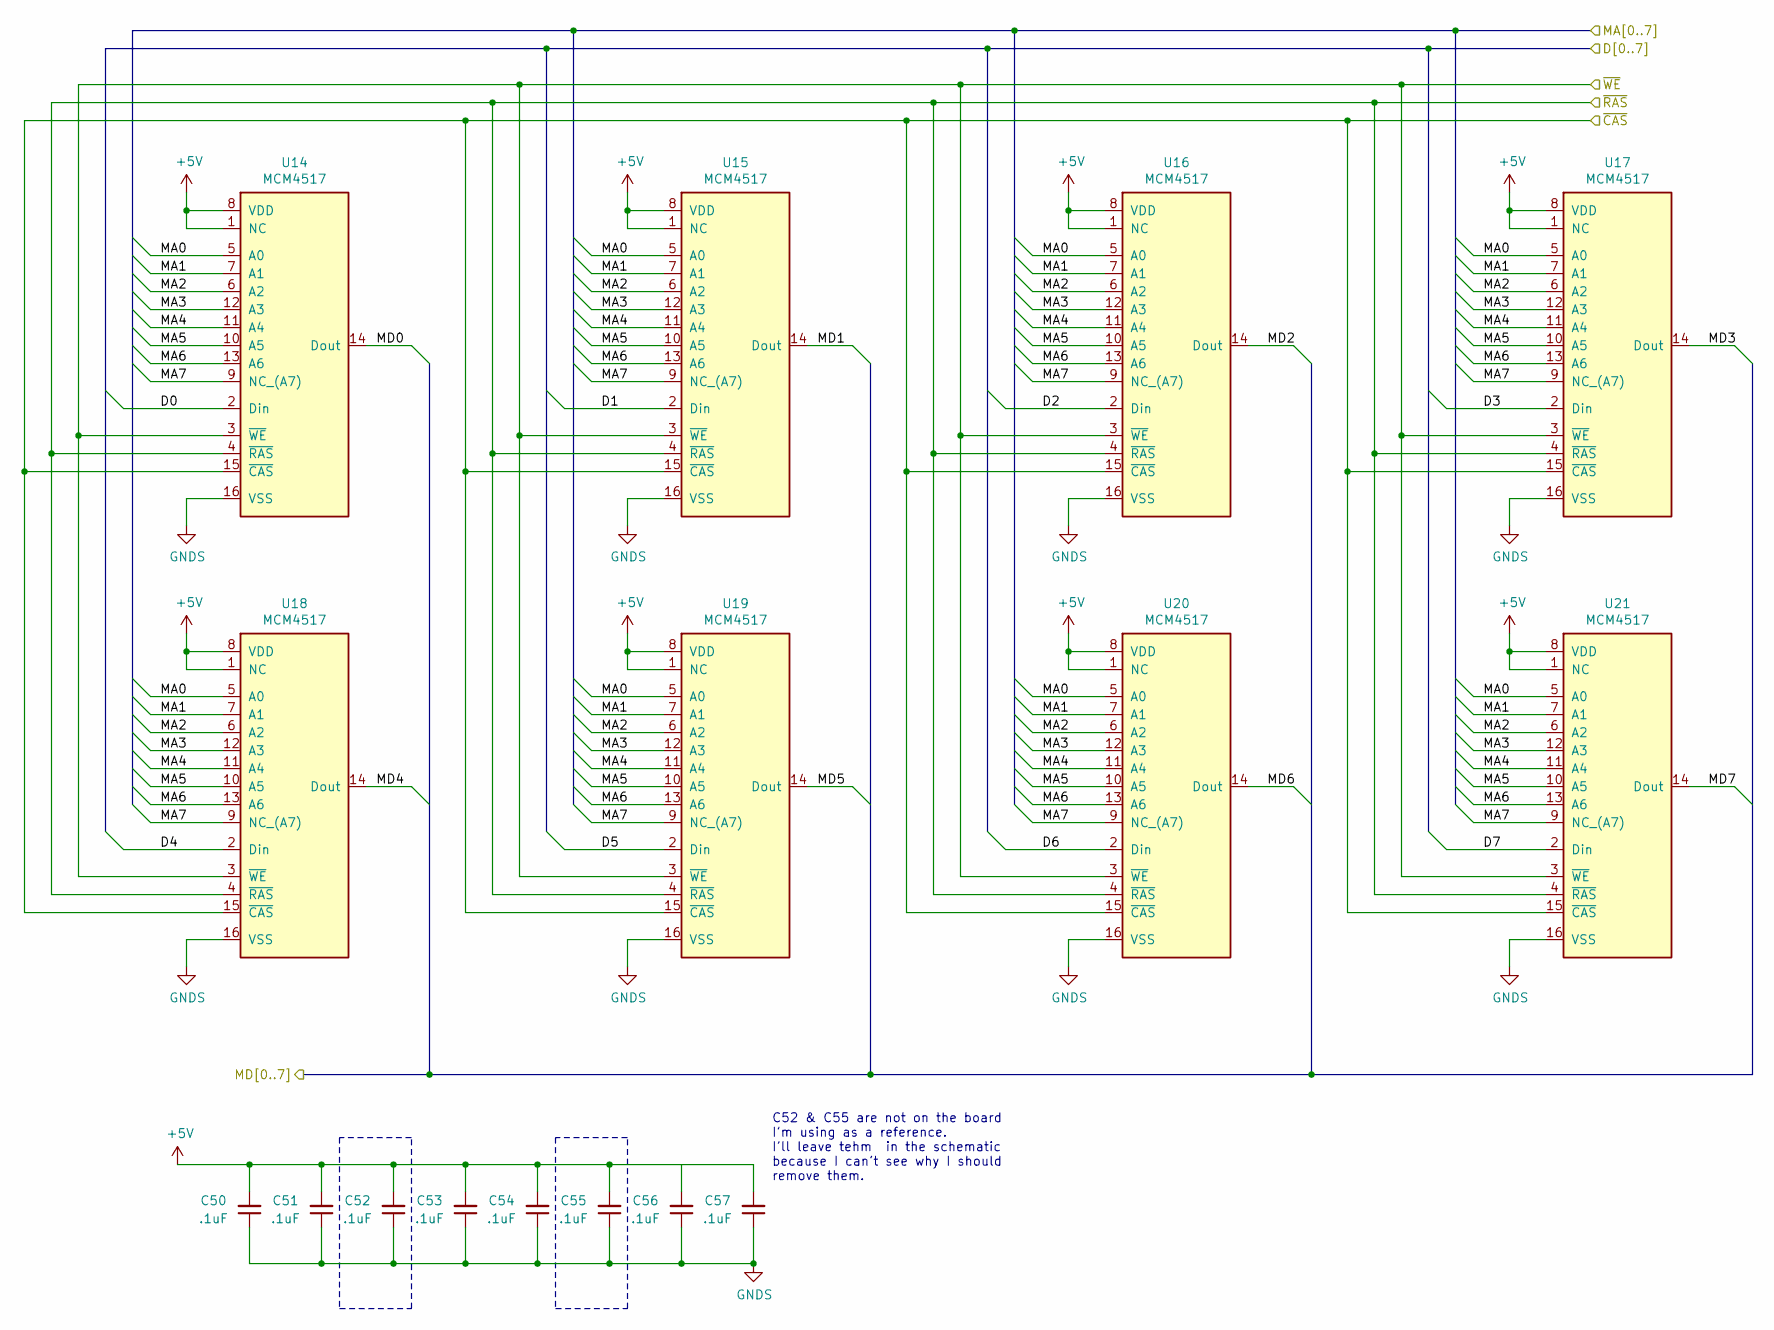
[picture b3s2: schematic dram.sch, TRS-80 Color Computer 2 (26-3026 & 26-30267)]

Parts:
C50, C51, C52, C53, C54, C55, C56, C57: .1uF; C_Axial_L3.8mm_D2.6mm_P10.00mm_Horizontal; Manufacturer part# A104K15X7RF5TAA
U14, U15, U16, U17, U18, U19, U21: MCM4517; DIP-16_W7.62mm_Socket; Manufacturer part# 1-2199298-4
U20: MCM4517; DIP-16_W7.62mm_Socket

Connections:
+5V: C50.2, C51.2, C52.2, C53.2, C54.2, C55.2, C56.2, C57.2, U14.1 (NC), U14.8 (VDD), U15.1 (NC), U15.8 (VDD), U16.1 (NC), U16.8 (VDD), U17.1 (NC), U17.8 (VDD), U18.1 (NC), U18.8 (VDD), U19.1 (NC), U19.8 (VDD), U20.1 (NC), U20.8 (VDD), U21.1 (NC), U21.8 (VDD); also elsewhere on the board
/D0: U14.2 (Din); also elsewhere on the board
/D1: U15.2 (Din); also elsewhere on the board
/D2: U16.2 (Din); also elsewhere on the board
/D3: U17.2 (Din); also elsewhere on the board
/D4: U18.2 (Din); also elsewhere on the board
/D5: U19.2 (Din); also elsewhere on the board
/D6: U20.2 (Din); also elsewhere on the board
/D7: U21.2 (Din); also elsewhere on the board
/dram/MA0: U14.5 (A0), U15.5 (A0), U16.5 (A0), U17.5 (A0), U18.5 (A0), U19.5 (A0), U20.5 (A0), U21.5 (A0); also elsewhere on the board
/dram/MA1: U14.7 (A1), U15.7 (A1), U16.7 (A1), U17.7 (A1), U18.7 (A1), U19.7 (A1), U20.7 (A1), U21.7 (A1); also elsewhere on the board
/dram/MA2: U14.6 (A2), U15.6 (A2), U16.6 (A2), U17.6 (A2), U18.6 (A2), U19.6 (A2), U20.6 (A2), U21.6 (A2); also elsewhere on the board
/dram/MA3: U14.12 (A3), U15.12 (A3), U16.12 (A3), U17.12 (A3), U18.12 (A3), U19.12 (A3), U20.12 (A3), U21.12 (A3); also elsewhere on the board
/dram/MA4: U14.11 (A4), U15.11 (A4), U16.11 (A4), U17.11 (A4), U18.11 (A4), U19.11 (A4), U20.11 (A4), U21.11 (A4); also elsewhere on the board
/dram/MA5: U14.10 (A5), U15.10 (A5), U16.10 (A5), U17.10 (A5), U18.10 (A5), U19.10 (A5), U20.10 (A5), U21.10 (A5); also elsewhere on the board
/dram/MA6: U14.13 (A6), U15.13 (A6), U16.13 (A6), U17.13 (A6), U18.13 (A6), U19.13 (A6), U20.13 (A6), U21.13 (A6); also elsewhere on the board
/dram/MA7: U14.9 (NC_(A7)), U15.9 (NC_(A7)), U16.9 (NC_(A7)), U17.9 (NC_(A7)), U18.9 (NC_(A7)), U19.9 (NC_(A7)), U20.9 (NC_(A7)), U21.9 (NC_(A7)); also elsewhere on the board
/dram/MD0: U14.14 (Dout); also elsewhere on the board
/dram/MD1: U15.14 (Dout); also elsewhere on the board
/dram/MD2: U16.14 (Dout); also elsewhere on the board
/dram/MD3: U17.14 (Dout); also elsewhere on the board
/dram/MD4: U18.14 (Dout); also elsewhere on the board
/dram/MD5: U19.14 (Dout); also elsewhere on the board
/dram/MD6: U20.14 (Dout); also elsewhere on the board
/dram/MD7: U21.14 (Dout); also elsewhere on the board
/dram/~CAS: U14.15 (~CAS), U15.15 (~CAS), U16.15 (~CAS), U17.15 (~CAS), U18.15 (~CAS), U19.15 (~CAS), U20.15 (~CAS), U21.15 (~CAS); also elsewhere on the board
/dram/~RAS: U14.4 (~RAS), U15.4 (~RAS), U16.4 (~RAS), U17.4 (~RAS), U18.4 (~RAS), U19.4 (~RAS), U20.4 (~RAS), U21.4 (~RAS); also elsewhere on the board
/dram/~WE: U14.3 (~WE), U15.3 (~WE), U16.3 (~WE), U17.3 (~WE), U18.3 (~WE), U19.3 (~WE), U20.3 (~WE), U21.3 (~WE); also elsewhere on the board
GNDS: C50.1, C51.1, C52.1, C53.1, C54.1, C55.1, C56.1, C57.1, U14.16 (VSS), U15.16 (VSS), U16.16 (VSS), U17.16 (VSS), U18.16 (VSS), U19.16 (VSS), U20.16 (VSS), U21.16 (VSS); also elsewhere on the board

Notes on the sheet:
C52 & C55 are not on the board I'm using as a reference. I'll leave tehm in the schematic because I can't see why I should remove them.

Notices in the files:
parts and their libraries:
Copyright 2016 Accelerated Designs. All rights reserved.
Copyright 2021 Accelerated Designs. All rights reserved.
